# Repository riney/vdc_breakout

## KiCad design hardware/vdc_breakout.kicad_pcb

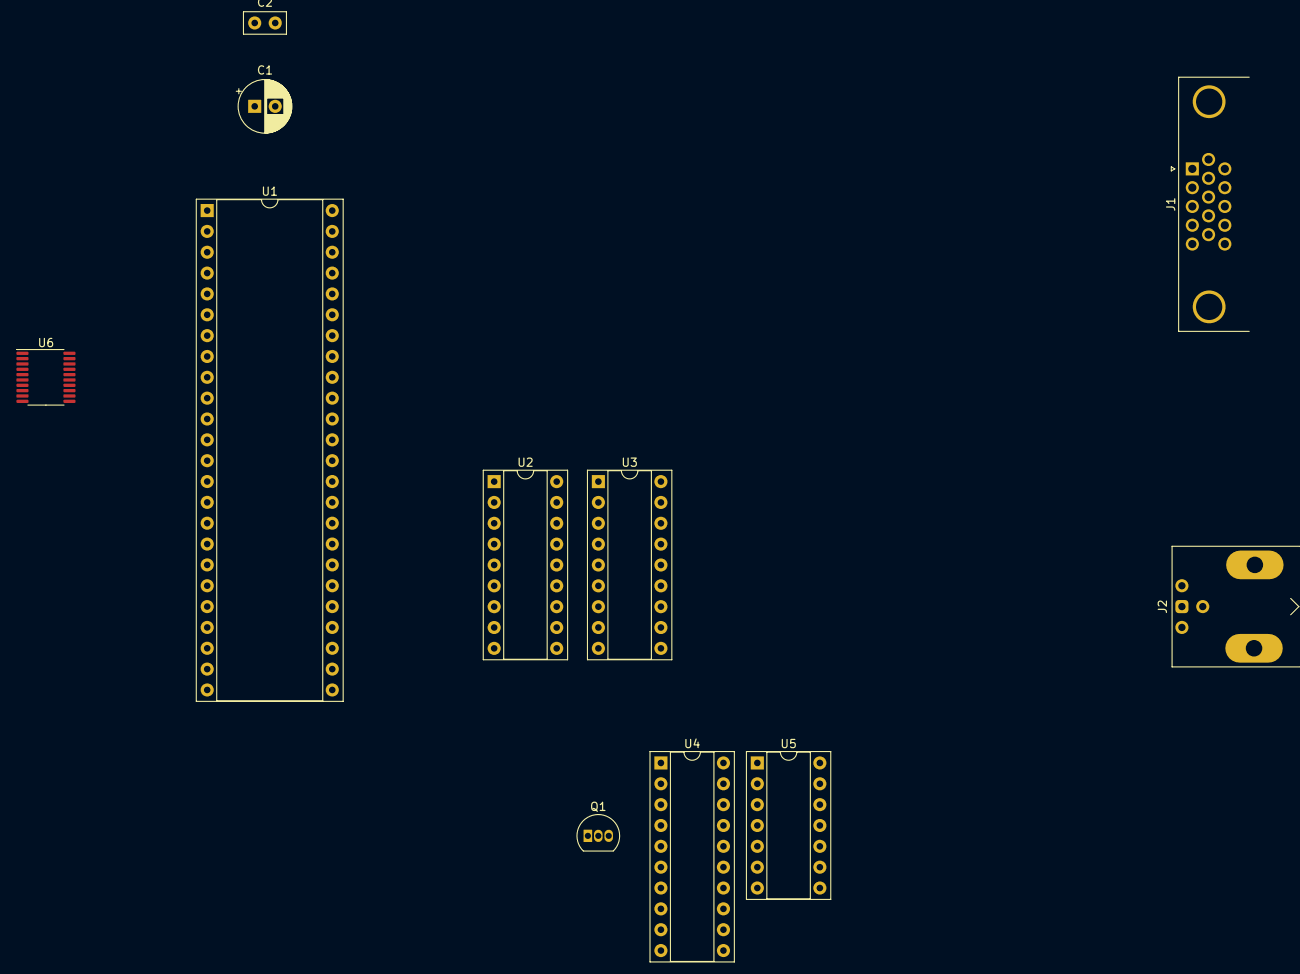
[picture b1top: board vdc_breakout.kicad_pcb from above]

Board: 2 copper layers, 11 parts (0 on the bottom side), 11 nets, no tracks yet.

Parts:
C1: 10uF 16v; CP_Radial_D6.3mm_P2.50mm
C2: C_Small; C_Disc_D5.0mm_W2.5mm_P2.50mm
J1: DE15_Receptacle_HighDensity_MountingHoles; DSUB-15-HD_Female_Horizontal_P2.29x1.98mm_EdgePinOffset3.03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
J2: Conn_Coaxial; BNC_Amphenol_031-6575_Horizontal
Q1: 2SC1815; TO-92_Inline
U1: DIP-48_W15.24mm_Socket
U2, U3: 41464; DIP-18_W7.62mm_Socket
U4: 74LS244; DIP-20_W7.62mm_Socket
U5: 7407; DIP-14_W7.62mm_Socket
U6: TXB0108PW; TSSOP-20_4.4x6.5mm_P0.65mm

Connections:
+5V: C1.1, C2.1, U1.12 (Vss)
/A0: U1.25 (LPEN), U2.14 (A0), U3.14 (A0)
/A1: U1.26 (DA0), U2.13 (A1), U3.13 (A1)
/A2: U1.27 (DA1), U2.12 (A2), U3.12 (A2)
/A3: U1.28 (DA2), U2.11 (A3), U3.11 (A3)
/A4: U1.29 (DA3), U2.8 (A4), U3.8 (A4)
/A5: U1.30 (DA4), U2.7 (A5), U3.7 (A5)
/A6: U1.31 (DA5), U2.6 (A6), U3.6 (A6)
/A7: U1.32 (DA6), U2.10 (A7), U3.10 (A7)
GND: C1.2, C2.2, U1.23 (INIT), U1.37 (Vcc), U2.18 (GND), U3.18 (GND)
VCC: U2.9 (VCC), U3.9 (VCC)

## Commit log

2024-02-24 Tested that libraries were moved correctly, and updated to KiCAD 8
